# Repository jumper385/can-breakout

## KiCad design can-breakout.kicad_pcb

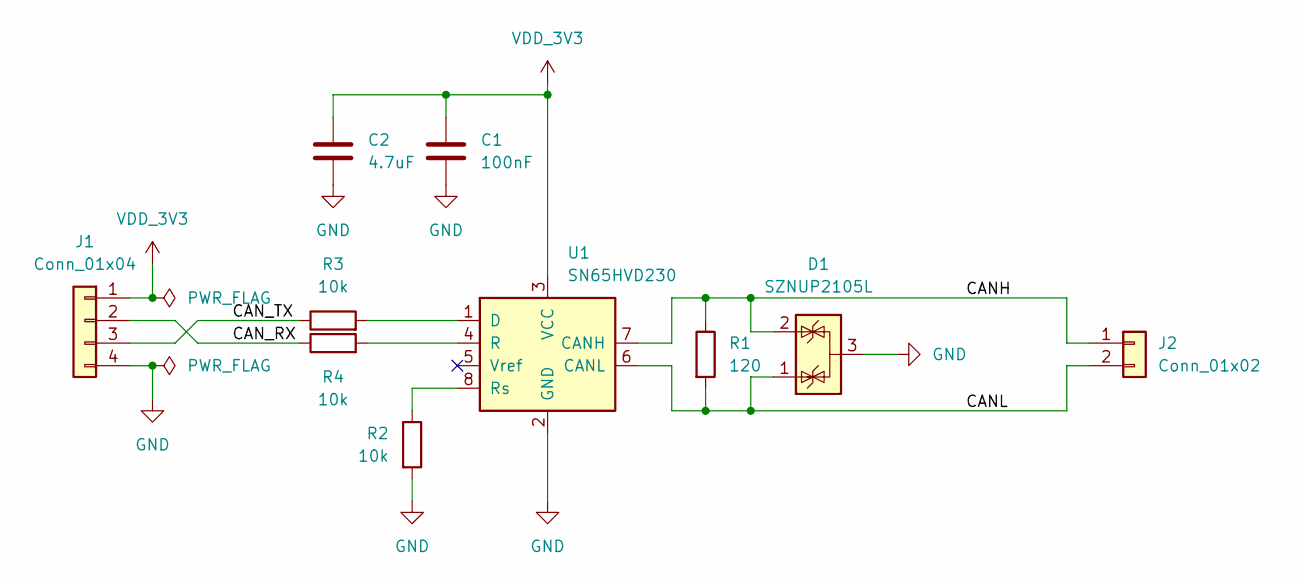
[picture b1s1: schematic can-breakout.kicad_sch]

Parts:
C1: 100nF; C_0402_1005Metric; JLC_PN C307331
C2: 4.7uF; C_0402_1005Metric; JLC_PN C23733
D1: SZNUP2105L; SOT-23; JLC_PN C20615827
J1: Conn_01x04; PinHeader_1x04_P2.54mm_Vertical
J2: Conn_01x02; JST_PH_B2B-PH-K_1x02_P2.00mm_Vertical; JLC_PN C131337
R1: 120; R_0402_1005Metric; JLC_PN C25079
R2, R3, R4: 10k; R_0402_1005Metric; JLC_PN C25744
U1: SN65HVD230; SOIC-8_3.9x4.9mm_P1.27mm; JLC_PN C12084

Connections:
/CANH: D1.2 (K), J2.1, R1.1, U1.7 (CANH)
/CANL: D1.1 (K), J2.2, R1.2, U1.6 (CANL)
/CAN_RX: J1.2, R4.1
/CAN_TX: J1.3, R3.1
GND: C1.2, C2.2, D1.3 (A), J1.4, R2.2, U1.2 (GND)
unnamed: R3.2, U1.1 (D)
unnamed: R4.2, U1.4 (R)
unnamed: R2.1, U1.8 (Rs)
VDD_3V3: C1.1, C2.1, J1.1, U1.3 (VCC)

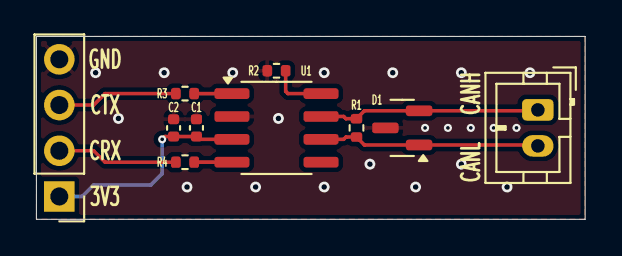
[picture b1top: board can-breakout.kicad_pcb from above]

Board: 2 copper layers, 30.5 x 10.2 mm, 10 parts (0 on the bottom side), 9 nets.

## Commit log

2026-03-12 feat: implemented breakout
2026-03-13 feat: completed board
2026-03-14 ci: creating artifact compilation with kibot
2026-03-14 fix: connecting current limiting resitors to sn65
2026-03-14 ci: adding version to artifacts
2026-03-14 ci: fix cz toml file
2026-03-14 bump: version 0.0.1 → 0.1.0
2026-03-14 ci: zipping generated only...
2026-03-14 ci: update release tarball creation to use renamed folder
2026-03-14 ci: adjust naming typo
2026-03-15 fix: added stitching to gnd plane between CANH and CANL diff pairs prior to outboard
2026-03-15 chore: re-running drc
